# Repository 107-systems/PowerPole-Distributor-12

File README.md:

`l3xz_power_distribution`
========================

power distribution board with power pole connectors for the [L3X-Z Hexapod](https://github.com/107-systems/l3xz-hw)

<p align="center">
  
</p>

<p align="center">
  </a>
</p>

## PCB
### Top

<p align="center">
  </a>
</p>

### Bottom

<p align="center">
  </a>
</p>

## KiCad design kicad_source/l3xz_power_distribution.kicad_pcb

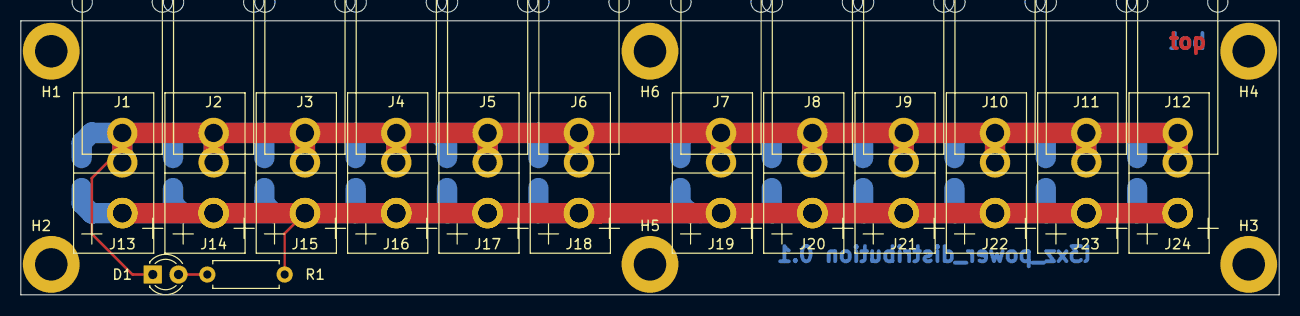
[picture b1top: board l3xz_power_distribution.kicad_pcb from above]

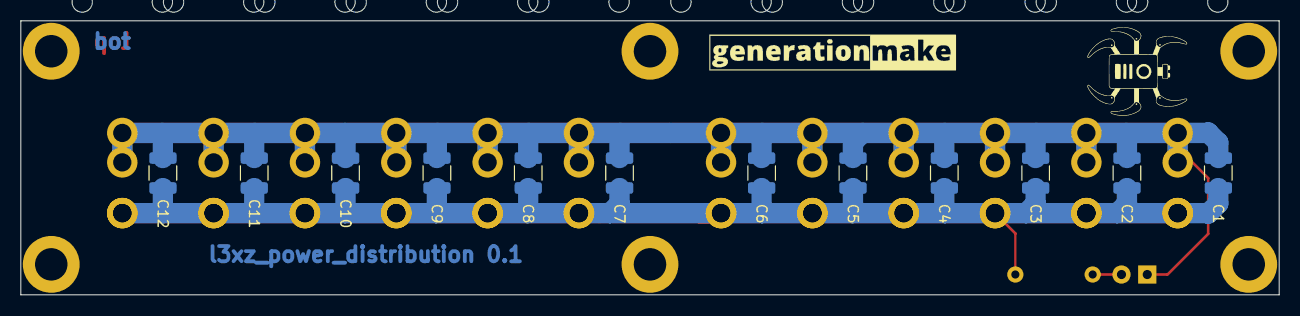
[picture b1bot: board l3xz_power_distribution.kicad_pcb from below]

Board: 2 copper layers, 124.0 x 27.0 mm, 46 parts (14 on the bottom side), 3 nets.

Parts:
C1, C2, C3, C4, C5, C6, C7, C8, C9, C10, C11, C12: 10 uF 25 V; C_1210_3225Metric
D1: LED_Small; LED_D3.0mm
H1, H2, H3, H4, H5, H6: MountingHole_Pad; MountingHole_3.2mm_M3_DIN965_Pad
J1, J2, J3, J4, J5, J6, J7, J8, J9, J10, J11, J12: PowerPole_ver; POWERPOLE_hor90_2
J13, J14, J15, J16, J17, J18, J19, J20, J21, J22, J23, J24: PowerPole_ver; POWERPOLE_2
L1: Label; generationmake_logo
L2: Label; l3xz_small_silk
R1: 10k; R_Axial_DIN0207_L6.3mm_D2.5mm_P7.62mm_Horizontal

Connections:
+BATT: C1.1, C2.1, C3.1, C4.1, C5.1, C6.1, C7.1, C8.1, C9.1, C10.1, C11.1, C12.1, J1.1, J2.1, J3.1, J4.1, J5.1, J6.1, J7.1, J8.1, J9.1, J10.1, J11.1, J12.1, J13.1, J14.1, J15.1, J16.1, J17.1, J18.1, J19.1, J20.1, J21.1, J22.1, J23.1, J24.1, R1.1
GND: C1.2, C2.2, C3.2, C4.2, C5.2, C6.2, C7.2, C8.2, C9.2, C10.2, C11.2, C12.2, D1.1 (K), J1.2, J2.2, J3.2, J4.2, J5.2, J6.2, J7.2, J8.2, J9.2, J10.2, J11.2, J12.2, J13.2, J14.2, J15.2, J16.2, J17.2, J18.2, J19.2, J20.2, J21.2, J22.2, J23.2, J24.2
unnamed: D1.2 (A), R1.2

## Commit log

2023-03-28 added kicad project
2023-03-28 added 4 more power poles
2023-03-29 added schematic pdf
2023-03-29 added images
2023-03-29 added some labels
2023-04-08 moved to horizontal power poles
2023-04-08 added mounting holes
2023-04-08 updated images and schematic pdf
2023-04-09 added additional mounting hole
2023-04-09 switched to THT for LED and resistor
2023-04-09 added alternative footprint for power pole
2023-04-09 added step file
2023-04-09 added freecad file
2023-04-09 added stl file
2023-04-16 added licence
